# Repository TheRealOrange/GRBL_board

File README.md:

# GRBL_board

## Introduction

This is a PCB designed to run [GRBL](https://github.com/gnea/grbl), an open source CNC control software that is designed and optimised for Arduino. This board uses [GRBL-Mega](https://github.com/gnea/grbl-Mega), which is a version of GRBL that can run on the ATMEGA-2560, used in the Arduino Mega. This implementation allows GRBL to have a larger buffer size, since the ATMEGA-328P that GRBL was originally designed for has severe memory limitations.

This board design incorporates several additional features, such as:

- Designed for SPI configured Trinamic stepper drivers such as the TMC5160, TMC2130, etc.
- Ability to change the mirrored axis (X, Y or Z) via software (supports software configurable gantry levelling)
- All inputs and limit switch inputs wired with optocouplers, designed for normally open switches
- Onboard 12V 2A regulator, accepting 20-32VDC input
- Speed control for industrial VFDs, with a standard 4-20mA current loop for spindle speed control
- Sink logic for spindle control
- Possible sensorless homing using Trinamic drivers (not ideal since it only emulates a limit switch)

The goal is to accomplish this with minimal editing of the GRBL code, thus to do so an additional ATMEGA-328P is added on the board to enable the additional features.

## Connections

This board is designed with the aim of being as compatible as possible with the default GRBL, and as such, the pins are wired to follow the default GRBL-Mega pinout, as shown.

## Trinamic Drivers

Trinamic stepper motor drivers are exceptional in terms of performance and efficiency, incorporating advanced features that enable steppers to run cooler and with near silent operation. 

However, the tricky bit is that they are not a plug an play solution unlike other stepper drivers like the DRV8825 or the A4988 drivers. The drivers haveto be configured whenever they are powered up. To accomplish this, the separate ATMEGA-328P is used to communicate with the drivers via SPI in order to configure them.

## Mirrored Axis

Most CNC configurations include one axis which has dual stepper drive. GRBL has limited support for axis mirroring, and usually sacrifices some pins, such as spindle speed control. Thus, via the use of multiplexer ICs and the separate ATMEGA-328P, code can be uploaded to the ATMEGA-328P in order to specify which axis to mirror and whether to do gantry levelling for that axis.

To accomplish gantry levelling, the ATMEGA-328P will check the two limit switches on the mirrored axis, and if only one switch is triggered, the corresponding stepper's STEP pin will be held low, preventing it from moving until both switches are triggered. Once both limit switches are triggered, the limit switch signal will be sent to the GRBL controller running on the ATMEGA-2560.

## Inputs

Previously, I had an extremely bad experience with EMI on the limit switch lines when building a CNC, thus I decided to include an optocoupler on each input of the CNC controller. Although the switches are still normally open, the optocoupler requires current to drive the LED and thus it is nearly impossible for EMI to trigger the optocoupler. This should make the CNC much more robust against EMI, and it is possible to change the switches to normally closed by modifying GRBL.

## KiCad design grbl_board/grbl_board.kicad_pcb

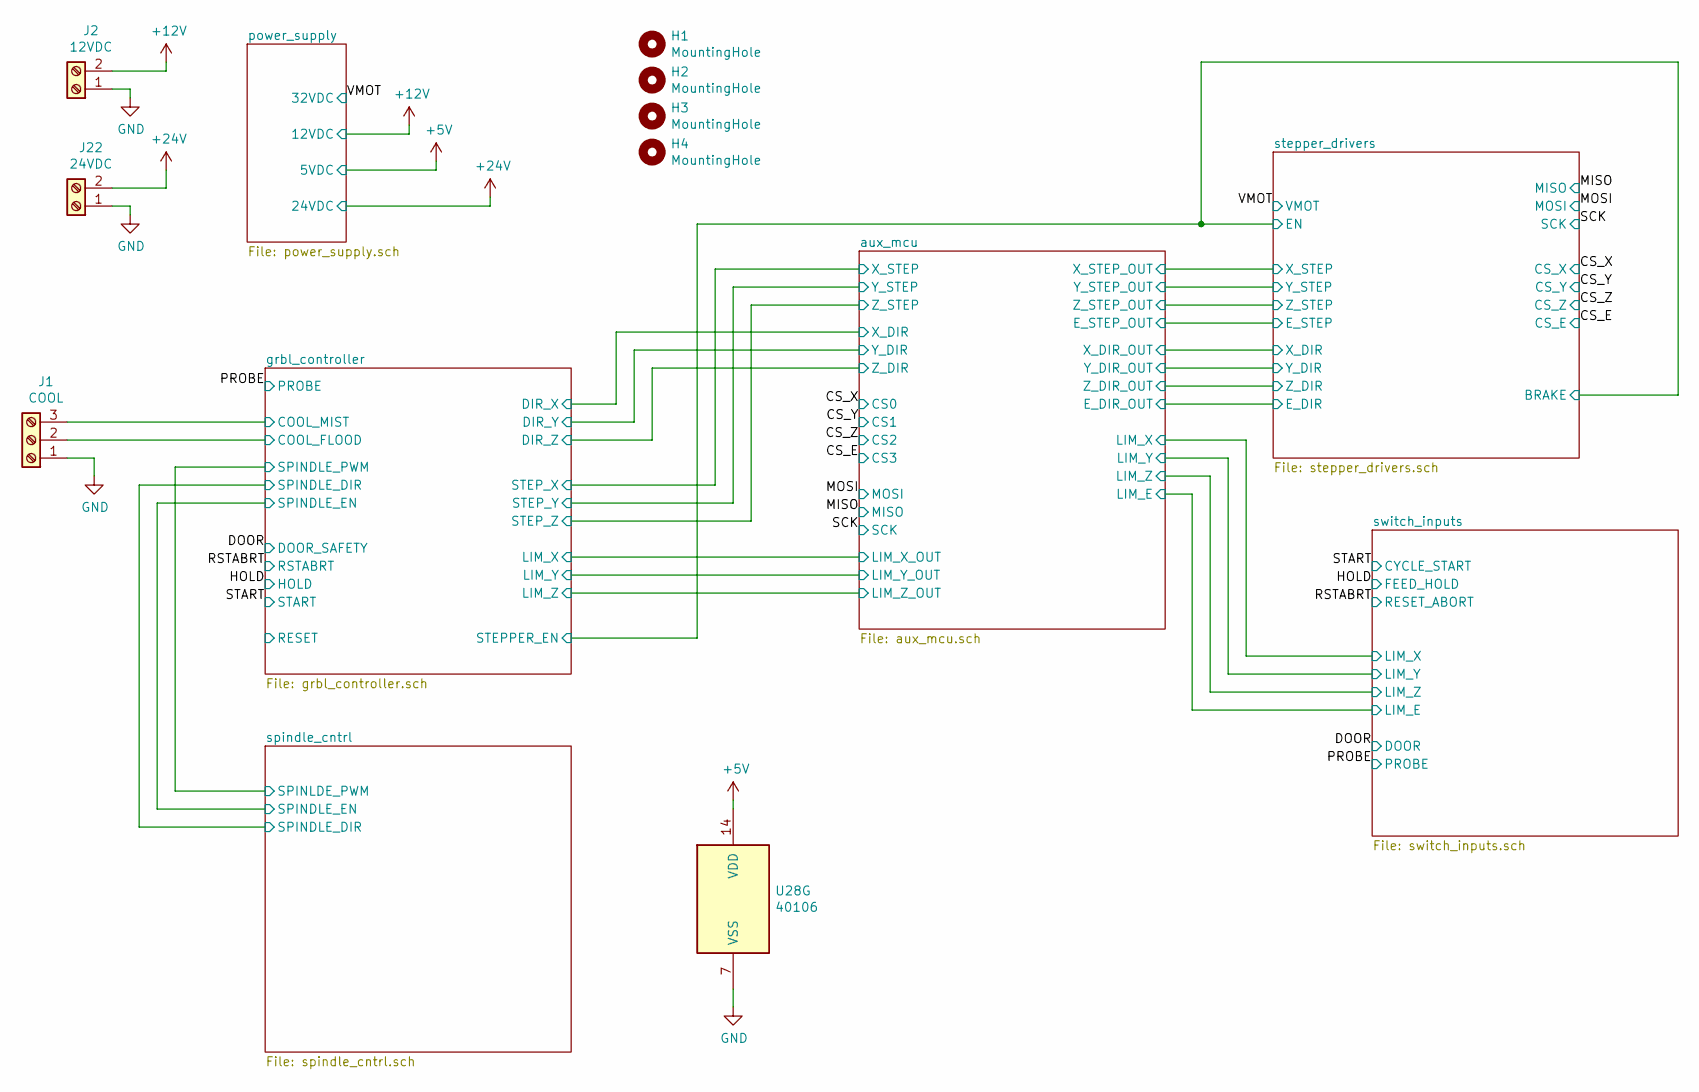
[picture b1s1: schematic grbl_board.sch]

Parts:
H1, H2, H3, H4: MountingHole; MountingHole_3.2mm_M3_Pad
J1: COOL; PhoenixContact_MC_1,5_3-G-3.81_1x03_P3.81mm_Horizontal; Digikey Part No. ED2809-ND
J2: 12VDC; PhoenixContact_MC_1,5_2-G-3.81_1x02_P3.81mm_Horizontal; Digikey Part No. ED2808-ND
J22: 24VDC; PhoenixContact_MC_1,5_2-G-3.81_1x02_P3.81mm_Horizontal; Digikey Part No. ED2808-ND
U28: 40106; TSSOP-14_4.4x5mm_P0.65mm; Digikey Part No. HEF40106BTT,112-ND

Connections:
+5V: U28.14 (VDD); also elsewhere on the board
+12V: J2.2; also elsewhere on the board
+24V: J22.2; also elsewhere on the board
/grbl_controller/COOL_FLOOD: J1.2; also elsewhere on the board
/grbl_controller/COOL_MIST: J1.3; also elsewhere on the board
GND: J1.1, J2.1, J22.1, U28.7 (VSS); also elsewhere on the board

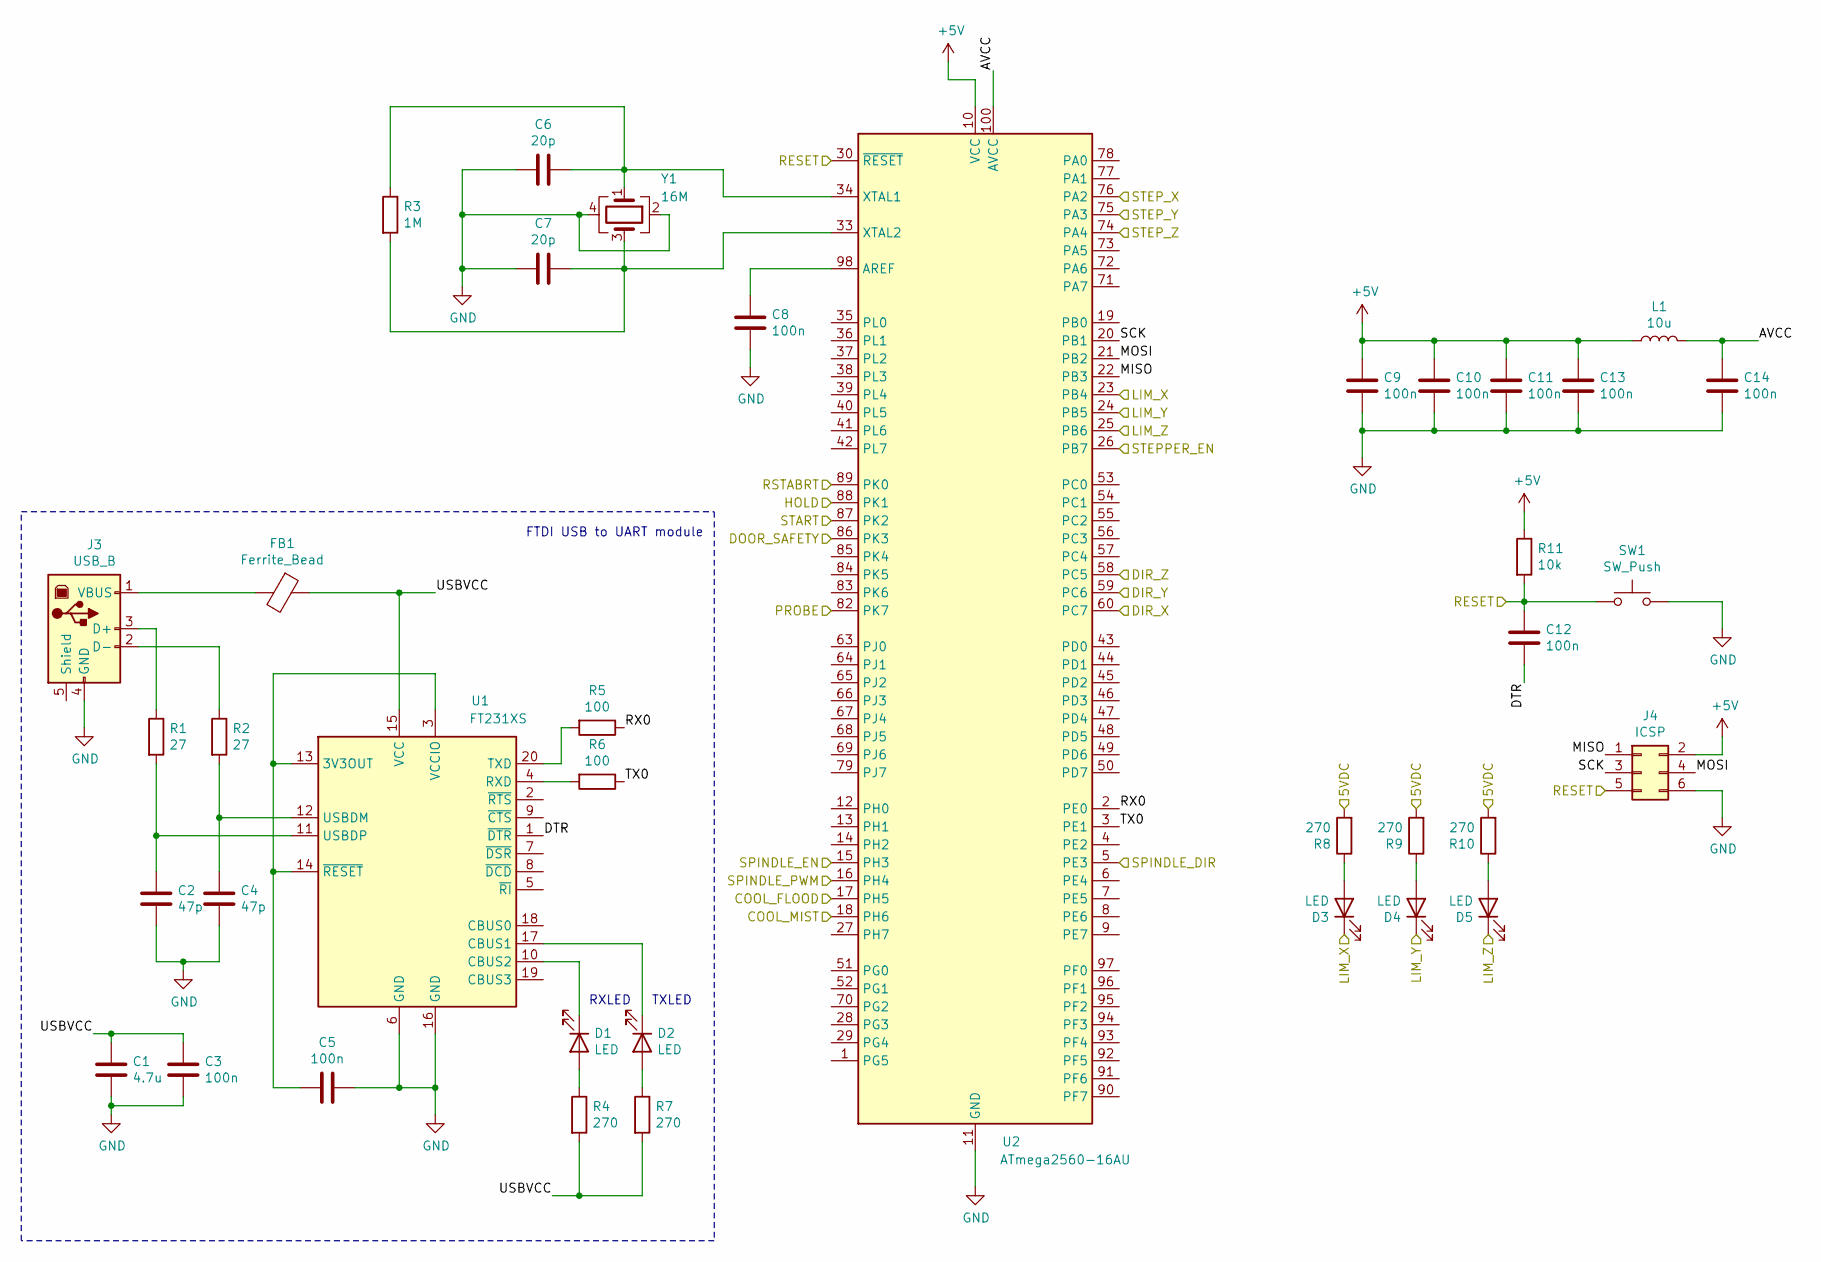
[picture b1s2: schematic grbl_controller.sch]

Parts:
C1: 4.7u; C_1206_3216Metric_Pad1.33x1.80mm_HandSolder; Digikey Part No. 1276-6781-1-ND
C2, C4: 47p; C_0402_1005Metric_Pad0.74x0.62mm_HandSolder; Digikey Part No. 1276-1699-1-ND
C3, C5, C8, C9, C10, C11, C12, C13, C14: 100n; C_0603_1608Metric_Pad1.05x0.95mm_HandSolder; Digikey Part No. 1276-1941-1-ND
C6, C7: 20p; C_0603_1608Metric_Pad1.05x0.95mm_HandSolder; Digikey Part No. 1276-1187-1-ND
D1, D2: LED; LED_1206_3216Metric_Pad1.42x1.75mm_HandSolder; Digikey Part No. 404-1042-1-ND
D3, D4, D5: LED; LED_1206_3216Metric_Pad1.42x1.75mm_HandSolder; Digikey Part No. 404-1046-1-ND
FB1: Ferrite_Bead; C_0603_1608Metric_Pad1.05x0.95mm_HandSolder; Digikey Part No. 732-1591-1-ND
J3: USB_B; USB_B_OST_USB-B1HSxx_Horizontal; Digikey Part No. 380-1492-ND
J4: ICSP; PinHeader_2x03_P2.54mm_Vertical; Digikey Part No. 609-3234-ND
L1: 10u; L_0805_2012Metric_Pad1.05x1.20mm_HandSolder; Digikey Part No. 490-4029-1-ND
R1, R2: 27; R_0603_1608Metric_Pad0.98x0.95mm_HandSolder; Digikey Part No. 311-27GRCT-ND
R3: 1M; R_0603_1608Metric_Pad0.98x0.95mm_HandSolder; Digikey Part No. 311-1.0MGRCT-ND
R4, R7, R8, R9, R10: 270; R_0805_2012Metric_Pad1.15x1.40mm_HandSolder; Digikey Part No. YAG6172CT-ND
R5, R6: 100; R_0603_1608Metric_Pad0.98x0.95mm_HandSolder; Digikey Part No. 311-100GRCT-ND
R11: 10k; R_0805_2012Metric_Pad1.15x1.40mm_HandSolder; Digikey Part No. 311-10KARCT-ND
SW1: SW_Push; SW_Push_1P1T_NO_6x6mm_H9.5mm; Digikey Part No. EG2526CT-ND
U1: FT231XS; SSOP-20_3.9x8.7mm_P0.635mm; Digikey Part No. 768-1129-1-ND
U2: ATmega2560-16AU; TQFP-100_14x14mm_P0.5mm; Digikey Part No. ATMEGA2560-16AU-ND
Y1: 16M; Crystal_SMD_SeikoEpson_TSX3225-4Pin_3.2x2.5mm_HandSoldering; Digikey Part No. SER4372CT-ND

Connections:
+5V: C9.1, C10.1, C11.1, C13.1, J4.2, L1.1, R11.1, U2.10 (VCC), U2.31 (VCC), U2.61 (VCC), U2.80 (VCC); also elsewhere on the board
/DOOR: U2.86 (PK3); also elsewhere on the board
/HOLD: U2.88 (PK1); also elsewhere on the board
/PROBE: U2.82 (PK7); also elsewhere on the board
/RSTABRT: U2.89 (PK0); also elsewhere on the board
/START: U2.87 (PK2); also elsewhere on the board
/grbl_controller/5VDC: R8.2, R9.2, R10.2
/grbl_controller/AVCC: C14.1, L1.2, U2.100 (AVCC)
/grbl_controller/COOL_FLOOD: U2.17 (PH5); also elsewhere on the board
/grbl_controller/COOL_MIST: U2.18 (PH6); also elsewhere on the board
/grbl_controller/DIR_X: U2.60 (PC7); also elsewhere on the board
/grbl_controller/DIR_Y: U2.59 (PC6); also elsewhere on the board
/grbl_controller/DIR_Z: U2.58 (PC5); also elsewhere on the board
/grbl_controller/DTR: C12.2, U1.1 (~DTR)
/grbl_controller/LIM_X: D3.1 (K), U2.23 (PB4); also elsewhere on the board
/grbl_controller/LIM_Y: D4.1 (K), U2.24 (PB5); also elsewhere on the board
/grbl_controller/LIM_Z: D5.1 (K), U2.25 (PB6); also elsewhere on the board
/grbl_controller/MISO: J4.1, U2.22 (PB3)
/grbl_controller/MOSI: J4.4, U2.21 (PB2)
/grbl_controller/RESET: C12.1, J4.5, R11.2, SW1.1, U2.30 (~RESET)
/grbl_controller/RX0: R5.1, U2.2 (PE0)
/grbl_controller/SCK: J4.3, U2.20 (PB1)
/grbl_controller/SPINDLE_DIR: U2.5 (PE3); also elsewhere on the board
/grbl_controller/SPINDLE_EN: U2.15 (PH3); also elsewhere on the board
/grbl_controller/SPINDLE_PWM: U2.16 (PH4); also elsewhere on the board
/grbl_controller/STEP_X: U2.76 (PA2); also elsewhere on the board
/grbl_controller/STEP_Y: U2.75 (PA3); also elsewhere on the board
/grbl_controller/STEP_Z: U2.74 (PA4); also elsewhere on the board
/grbl_controller/TX0: R6.1, U2.3 (PE1)
/grbl_controller/USBVCC: C1.1, C3.1, FB1.1, R4.2, R7.2, U1.15 (VCC)
/stepper_drivers/BRAKE: U2.26 (PB7); also elsewhere on the board
GND: C1.2, C2.2, C3.2, C4.2, C5.1, C6.2, C7.2, C8.1, C9.2, C10.2, C11.2, C13.2, C14.2, J3.4 (GND), J4.6, SW1.2, U1.6 (GND), U1.16 (GND), U2.11 (GND), U2.32 (GND), U2.62 (GND), U2.81 (GND), U2.99 (GND), Y1.2, Y1.4; also elsewhere on the board
unnamed: C2.1, R1.2, U1.11 (USBDP)
unnamed: C4.1, R2.2, U1.12 (USBDM)
unnamed: C5.2, U1.3 (VCCIO), U1.13 (3V3OUT), U1.14 (~RESET)
unnamed: C6.1, R3.1, U2.34 (XTAL1), Y1.1
unnamed: C7.1, R3.2, U2.33 (XTAL2), Y1.3
unnamed: C8.2, U2.98 (AREF)
unnamed: D1.1 (K), U1.10 (CBUS2)
unnamed: D1.2 (A), R4.1
unnamed: D2.1 (K), U1.17 (CBUS1)
unnamed: D2.2 (A), R7.1
unnamed: D3.2 (A), R8.1
unnamed: D4.2 (A), R9.1
unnamed: D5.2 (A), R10.1
unnamed: FB1.2, J3.1 (VBUS)
unnamed: J3.2 (D-), R2.1
unnamed: J3.3 (D+), R1.1
unnamed: R5.2, U1.20 (TXD)
unnamed: R6.2, U1.4 (RXD)

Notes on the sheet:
TXLED
RXLED
FTDI USB to UART module

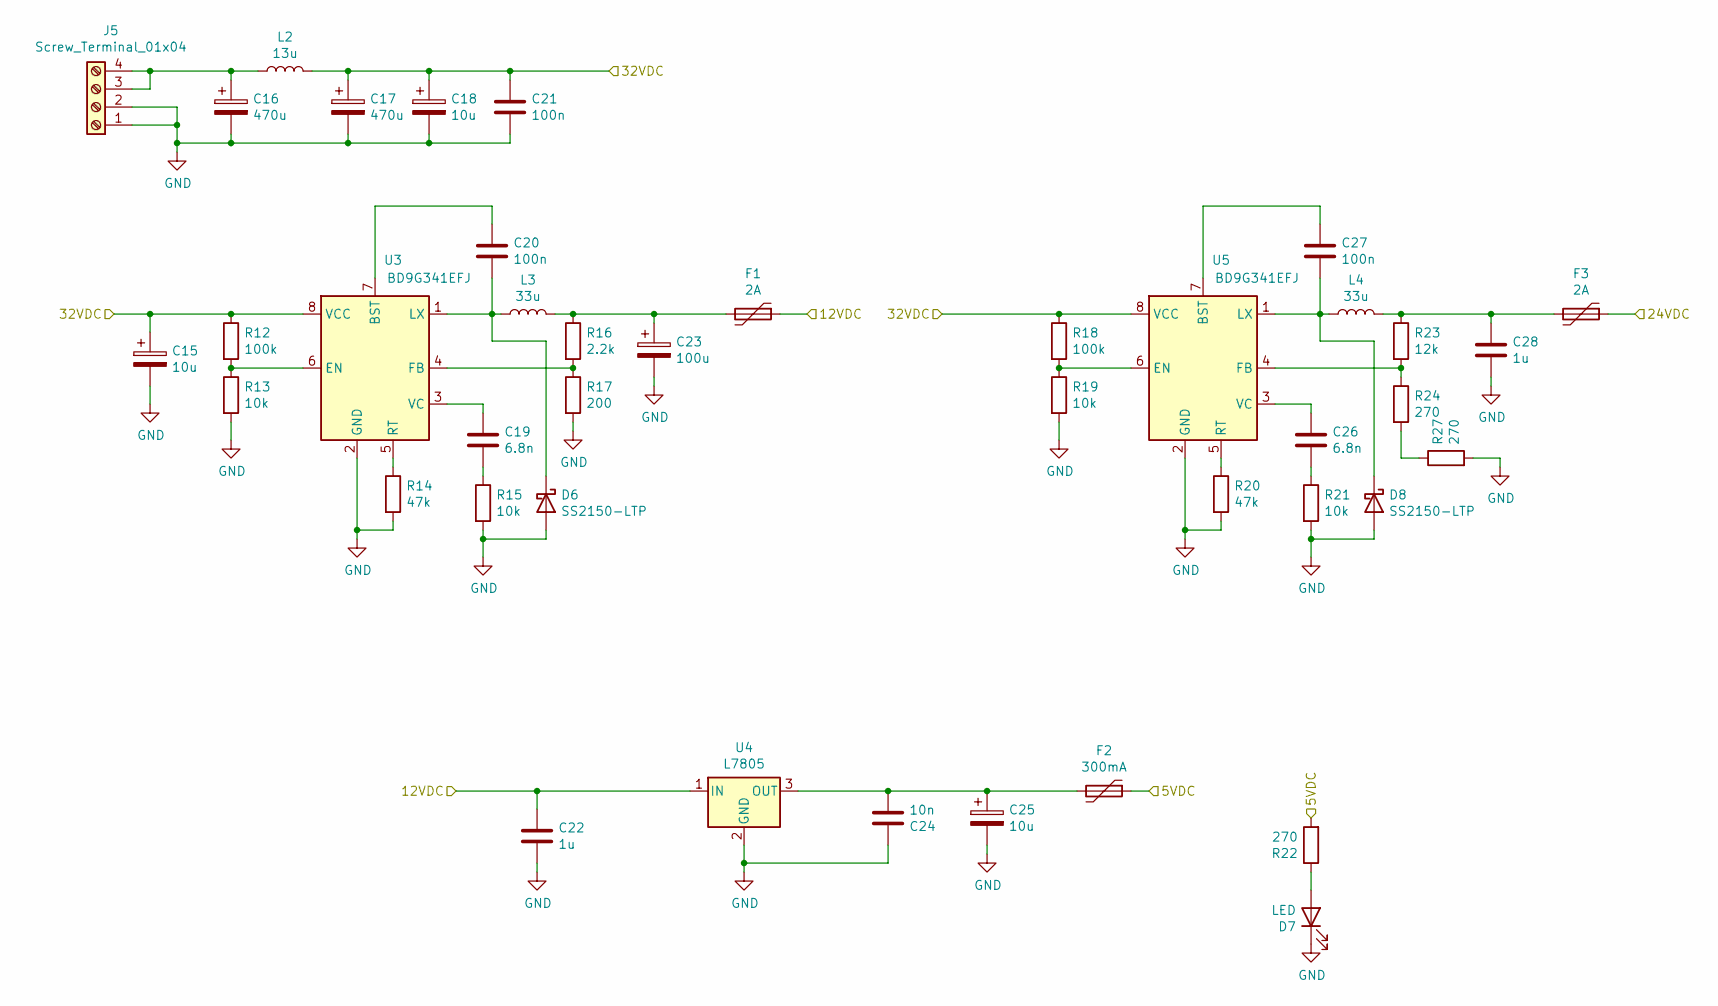
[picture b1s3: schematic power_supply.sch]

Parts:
C15, C18, C25: 10u; CP_Radial_D8.0mm_P3.50mm; Digikey Part No. 495-75596-ND
C16, C17: 470u; CP_Radial_D12.5mm_P5.00mm; Digikey Part No. 495-76603-ND
C19, C26: 6.8n; C_0402_1005Metric_Pad0.74x0.62mm_HandSolder; Digikey Part No. 1276-CL05B682KB5VPNCCT-ND
C20, C21, C27: 100n; C_0603_1608Metric_Pad1.05x0.95mm_HandSolder; Digikey Part No. 1276-1941-1-ND
C22, C28: 1u; C_1206_3216Metric_Pad1.33x1.80mm_HandSolder; Digikey Part No. 1276-1204-1-ND
C23: 100u; CP_Radial_D8.0mm_P3.50mm; Digikey Part No. 399-6119-ND
C24: 10n; C_0603_1608Metric_Pad1.08x0.95mm_HandSolder; Digikey Part No. 1276-1009-1-ND
D6, D8: SS2150-LTP; D_SMA_Handsoldering; Digikey Part No. SS2150-LTPMSCT-ND
D7: LED; LED_1206_3216Metric_Pad1.42x1.75mm_HandSolder; Digikey Part No. 404-1046-1-ND
F1, F3: 2A; Fuse_Bourns_MF-RHT200; Digikey Part No. 118-MF-RHT200/32-0-ND
F2: 300mA; Fuse_1812_4532Metric_Castellated; Digikey Part No. 507-1758-1-ND
J5: Screw_Terminal_01x04; PhoenixContact_MC_1,5_4-G-3.81_1x04_P3.81mm_Horizontal; Digikey Part No. ED2810-ND
L2: 13u; L_Wuerth_HCI-1365; Digikey Part No. 732-1140-1-ND
L3, L4: 33u; L_Vishay_IHLP-4040; Digikey Part No. 541-2273-1-ND
R12, R18: 100k; R_0603_1608Metric_Pad0.98x0.95mm_HandSolder; Digikey Part No. 311-100KGRCT-ND
R13, R15, R19, R21: 10k; R_0805_2012Metric_Pad1.15x1.40mm_HandSolder; Digikey Part No. 311-10KARCT-ND
R14, R20: 47k; R_0805_2012Metric_Pad1.15x1.40mm_HandSolder; Digikey Part No. 311-47KARCT-ND
R16: 2.2k; R_0603_1608Metric_Pad0.98x0.95mm_HandSolder; Digikey Part No. 311-2.2KGRCT-ND
R17: 200; R_0603_1608Metric_Pad0.98x0.95mm_HandSolder; Digikey Part No. 311-200GRCT-ND
R22, R24, R27: 270; R_0805_2012Metric_Pad1.15x1.40mm_HandSolder; Digikey Part No. YAG6172CT-ND
R23: 12k; R_0805_2012Metric_Pad1.15x1.40mm_HandSolder; Digikey Part No. 311-12KARCT-ND
U3, U5: BD9G341EFJ; HTSOP-8-1EP_3.9x4.9mm_P1.27mm_EP2.4x3.2mm_ThermalVias; Digikey Part No. BD9G341AEFJ-E2CT-ND
U4: L7805; TO-263-2; Digikey Part No. 497-1170-1-ND

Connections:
+5V: F2.1, R22.2; also elsewhere on the board
+12V: C22.1, F1.1, U4.1 (IN); also elsewhere on the board
+24V: F3.1; also elsewhere on the board
/VMOT: C15.1, C17.1, C18.1, C21.1, L2.2, R12.1, R18.1, U3.8 (VCC), U5.8 (VCC); also elsewhere on the board
GND: C15.2, C16.2, C17.2, C18.2, C21.2, C22.2, C23.2, C24.1, C25.2, C28.2, D6.2 (A), D7.1 (K), D8.2 (A), J5.1, J5.2, R13.2, R14.2, R15.2, R17.2, R19.2, R20.2, R21.2, R27.2, U3.2 (GND), U4.2 (GND), U5.2 (GND); also elsewhere on the board
unnamed: C16.1, J5.3, J5.4, L2.1
unnamed: C19.1, U3.3 (VC)
unnamed: C19.2, R15.1
unnamed: C20.1, U3.7 (BST)
unnamed: C20.2, D6.1 (K), L3.1, U3.1 (LX)
unnamed: C23.1, F1.2, L3.2, R16.1
unnamed: C24.2, C25.1, F2.2, U4.3 (OUT)
unnamed: C26.1, U5.3 (VC)
unnamed: C26.2, R21.1
unnamed: C27.1, U5.7 (BST)
unnamed: C27.2, D8.1 (K), L4.1, U5.1 (LX)
unnamed: C28.1, F3.2, L4.2, R23.1
unnamed: D7.2 (A), R22.1
unnamed: R12.2, R13.1, U3.6 (EN)
unnamed: R14.1, U3.5 (RT)
unnamed: R16.2, R17.1, U3.4 (FB)
unnamed: R18.2, R19.1, U5.6 (EN)
unnamed: R20.1, U5.5 (RT)
unnamed: R23.2, R24.1, U5.4 (FB)
unnamed: R24.2, R27.1

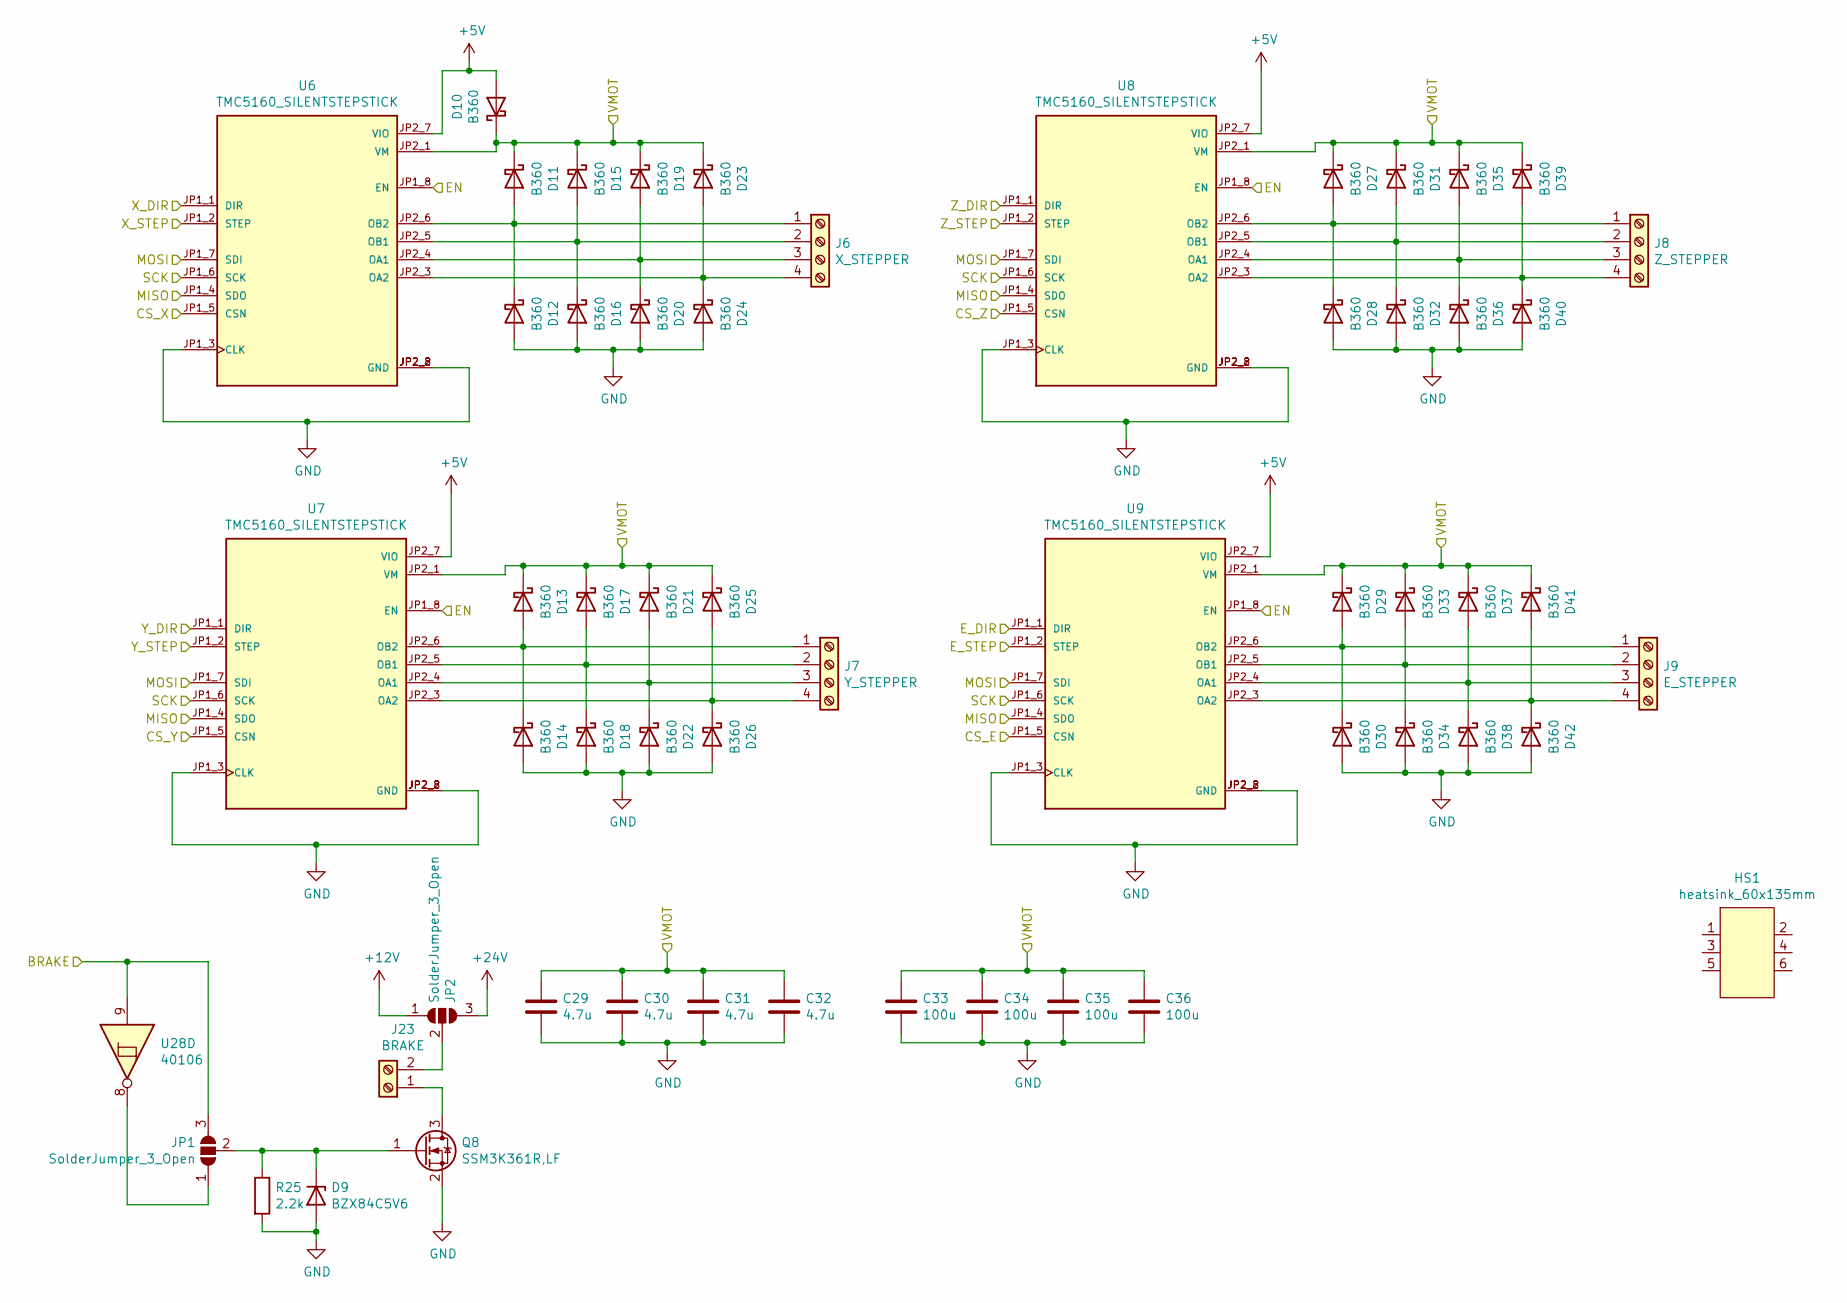
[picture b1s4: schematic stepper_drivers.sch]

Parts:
C29, C30, C31, C32: 4.7u; C_1206_3216Metric_Pad1.33x1.80mm_HandSolder; Digikey Part No. 1276-6781-1-ND
C33, C34, C35, C36: 100u; CP_Elec_8x10; Digikey Part No. UE107M050HFKTA
D9: BZX84C5V6; D_SOT-23_ANK; Digikey Part No. 1514-BZX84C5V6TRPBFREECT-ND
D10, D11, D12, D13, D14, D15, D16, D17, D18, D19, D20, D21, D22, D23, D24, D25, D26, D27, D28, D29, D30, D31, D32, D33, D34, D35, D36, D37, D38, D39, D40, D41, D42: B360; D_SMA_Handsoldering; Digikey Part No. CD214A-B360RCT-ND
HS1: heatsink_60x135mm
J6: X_STEPPER; PhoenixContact_MC_1,5_4-G-3.81_1x04_P3.81mm_Horizontal; Digikey Part No. ED2810-ND
J7: Y_STEPPER; PhoenixContact_MC_1,5_4-G-3.81_1x04_P3.81mm_Horizontal; Digikey Part No. ED2810-ND
J8: Z_STEPPER; PhoenixContact_MC_1,5_4-G-3.81_1x04_P3.81mm_Horizontal; Digikey Part No. ED2810-ND
J9: E_STEPPER; PhoenixContact_MC_1,5_4-G-3.81_1x04_P3.81mm_Horizontal; Digikey Part No. ED2810-ND
J23: BRAKE; PhoenixContact_MC_1,5_2-G-3.81_1x02_P3.81mm_Horizontal; Digikey Part No. ED2808-ND
JP1, JP2: SolderJumper_3_Open; SolderJumper-3_P1.3mm_Open_RoundedPad1.0x1.5mm
Q8: SSM3K361R,LF; SOT-23; Digikey Part No. SSM3K361RLFCT-ND
R25: 2.2k; R_0603_1608Metric_Pad0.98x0.95mm_HandSolder; Digikey Part No. 311-2.2KGRCT-ND
U6, U7, U8, U9: TMC5160_SILENTSTEPSTICK; PARTREV v11; Digikey Part No. 1460-TMC5160SILENTSTEPSTICK-ND
U28: 40106

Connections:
+5V: D10.2 (A), U6.JP2_7 (VIO), U7.JP2_7 (VIO), U8.JP2_7 (VIO), U9.JP2_7 (VIO); also elsewhere on the board
+12V: JP2.1 (A); also elsewhere on the board
+24V: JP2.3 (B); also elsewhere on the board
/CS_E: U9.JP1_5 (CSN); also elsewhere on the board
/CS_X: U6.JP1_5 (CSN); also elsewhere on the board
/CS_Y: U7.JP1_5 (CSN); also elsewhere on the board
/CS_Z: U8.JP1_5 (CSN); also elsewhere on the board
/MISO: U6.JP1_4 (SDO), U7.JP1_4 (SDO), U8.JP1_4 (SDO), U9.JP1_4 (SDO); also elsewhere on the board
/MOSI: U6.JP1_7 (SDI), U7.JP1_7 (SDI), U8.JP1_7 (SDI), U9.JP1_7 (SDI); also elsewhere on the board
/SCK: U6.JP1_6 (SCK), U7.JP1_6 (SCK), U8.JP1_6 (SCK), U9.JP1_6 (SCK); also elsewhere on the board
/VMOT: C29.1, C30.1, C31.1, C32.1, C33.1, C34.1, C35.1, C36.1, D10.1 (K), D11.1 (K), D13.1 (K), D15.1 (K), D17.1 (K), D19.1 (K), D21.1 (K), D23.1 (K), D25.1 (K), D27.1 (K), D29.1 (K), D31.1 (K), D33.1 (K), D35.1 (K), D37.1 (K), D39.1 (K), D41.1 (K), U6.JP2_1 (VM), U7.JP2_1 (VM), U8.JP2_1 (VM), U9.JP2_1 (VM); also elsewhere on the board
/grbl_controller/DIR_X: U6.JP1_1 (DIR); also elsewhere on the board
/grbl_controller/DIR_Y: U7.JP1_1 (DIR); also elsewhere on the board
/grbl_controller/DIR_Z: U8.JP1_1 (DIR); also elsewhere on the board
/stepper_drivers/BRAKE: JP1.3 (B), U6.JP1_8 (EN), U7.JP1_8 (EN), U8.JP1_8 (EN), U9.JP1_8 (EN), U28.9; also elsewhere on the board
/stepper_drivers/E_DIR: U9.JP1_1 (DIR); also elsewhere on the board
/stepper_drivers/E_STEP: U9.JP1_2 (STEP); also elsewhere on the board
/stepper_drivers/X_STEP: U6.JP1_2 (STEP); also elsewhere on the board
/stepper_drivers/Y_STEP: U7.JP1_2 (STEP); also elsewhere on the board
/stepper_drivers/Z_STEP: U8.JP1_2 (STEP); also elsewhere on the board
GND: C29.2, C30.2, C31.2, C32.2, C33.2, C34.2, C35.2, C36.2, D9.2 (A), D12.2 (A), D14.2 (A), D16.2 (A), D18.2 (A), D20.2 (A), D22.2 (A), D24.2 (A), D26.2 (A), D28.2 (A), D30.2 (A), D32.2 (A), D34.2 (A), D36.2 (A), D38.2 (A), D40.2 (A), D42.2 (A), Q8.2 (S), R25.2, U6.JP1_3 (CLK), U6.JP2_2 (GND), U6.JP2_8 (GND), U7.JP1_3 (CLK), U7.JP2_2 (GND), U7.JP2_8 (GND), U8.JP1_3 (CLK), U8.JP2_2 (GND), U8.JP2_8 (GND), U9.JP1_3 (CLK), U9.JP2_2 (GND), U9.JP2_8 (GND); also elsewhere on the board
unnamed: D9.1 (K), JP1.2 (C), Q8.1 (G), R25.1
unnamed: D11.2 (A), D12.1 (K), J6.1, U6.JP2_6 (OB2)
unnamed: D13.2 (A), D14.1 (K), J7.1, U7.JP2_6 (OB2)
unnamed: D15.2 (A), D16.1 (K), J6.2, U6.JP2_5 (OB1)
unnamed: D17.2 (A), D18.1 (K), J7.2, U7.JP2_5 (OB1)
unnamed: D19.2 (A), D20.1 (K), J6.3, U6.JP2_4 (OA1)
unnamed: D21.2 (A), D22.1 (K), J7.3, U7.JP2_4 (OA1)
unnamed: D23.2 (A), D24.1 (K), J6.4, U6.JP2_3 (OA2)
unnamed: D25.2 (A), D26.1 (K), J7.4, U7.JP2_3 (OA2)
unnamed: D27.2 (A), D28.1 (K), J8.1, U8.JP2_6 (OB2)
unnamed: D29.2 (A), D30.1 (K), J9.1, U9.JP2_6 (OB2)
unnamed: D31.2 (A), D32.1 (K), J8.2, U8.JP2_5 (OB1)
unnamed: D33.2 (A), D34.1 (K), J9.2, U9.JP2_5 (OB1)
unnamed: D35.2 (A), D36.1 (K), J8.3, U8.JP2_4 (OA1)
unnamed: D37.2 (A), D38.1 (K), J9.3, U9.JP2_4 (OA1)
unnamed: D39.2 (A), D40.1 (K), J8.4, U8.JP2_3 (OA2)
unnamed: D41.2 (A), D42.1 (K), J9.4, U9.JP2_3 (OA2)
unnamed: J23.1, Q8.3 (D)
unnamed: J23.2, JP2.2 (C)
unnamed: JP1.1 (A), U28.8

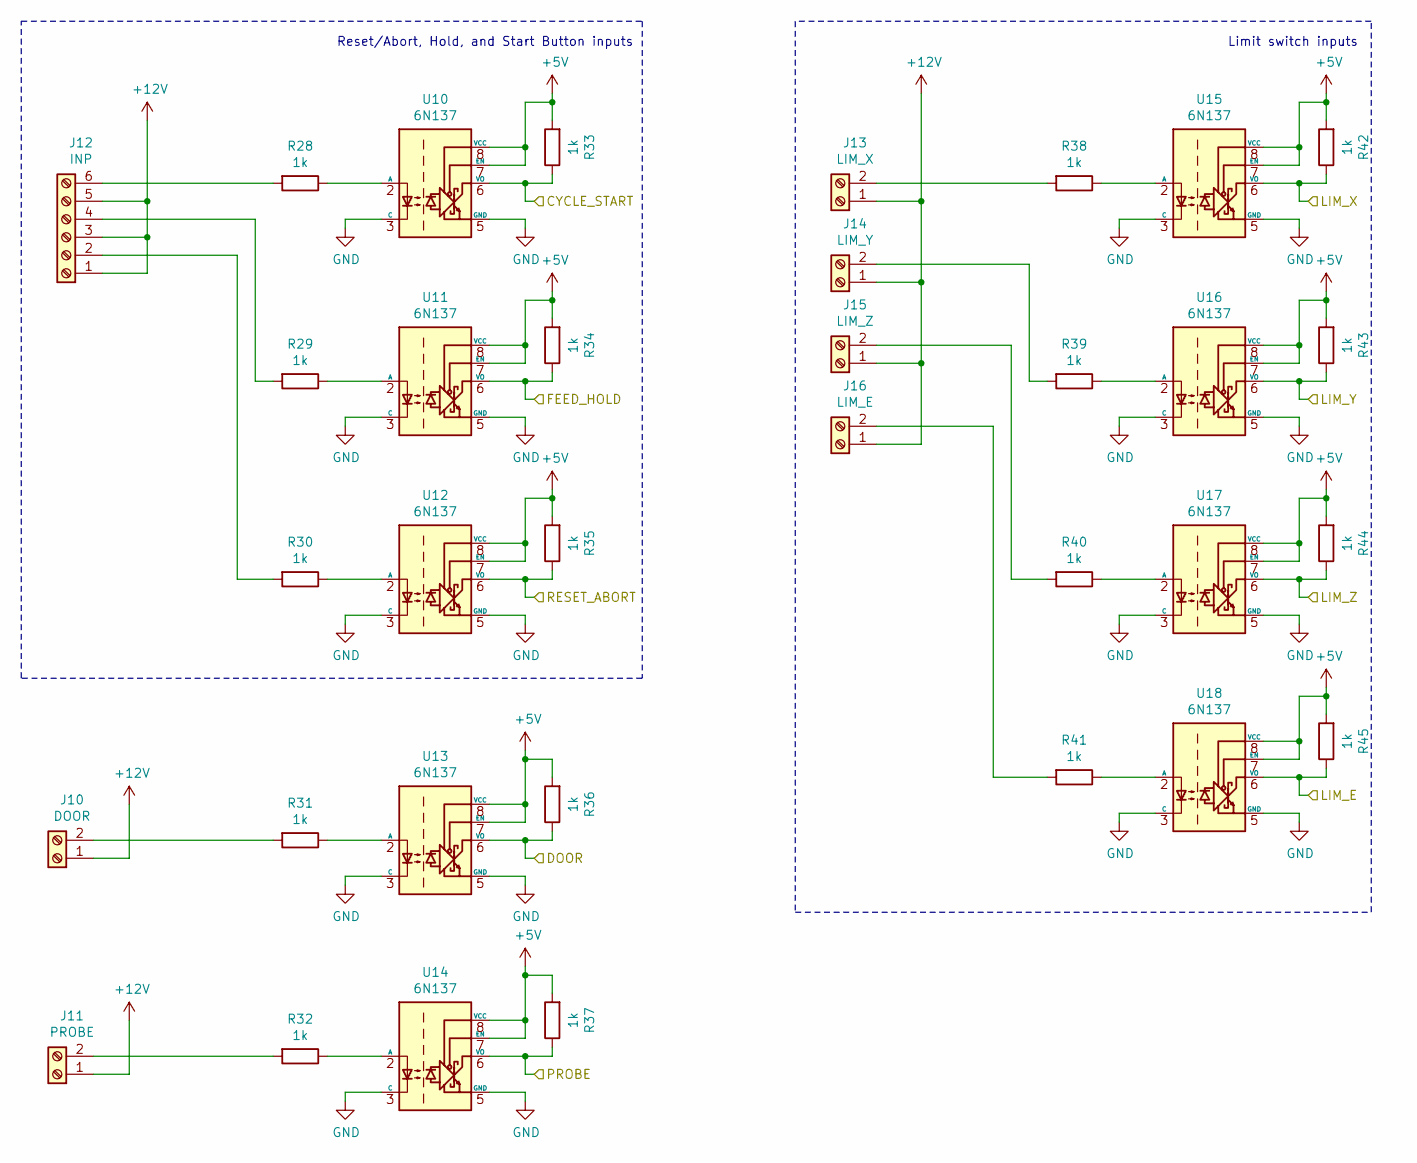
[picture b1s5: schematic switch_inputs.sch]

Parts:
J10: DOOR; PhoenixContact_MC_1,5_2-G-3.81_1x02_P3.81mm_Horizontal; Digikey Part No. ED2808-ND
J11: PROBE; PhoenixContact_MC_1,5_2-G-3.81_1x02_P3.81mm_Horizontal; Digikey Part No. ED2808-ND
J12: INP; PhoenixContact_MC_1,5_6-G-3.81_1x06_P3.81mm_Horizontal; Digikey Part No. ED2812-ND
J13: LIM_X; PhoenixContact_MC_1,5_2-G-3.81_1x02_P3.81mm_Horizontal; Digikey Part No. ED2808-ND
J14: LIM_Y; PhoenixContact_MC_1,5_2-G-3.81_1x02_P3.81mm_Horizontal; Digikey Part No. ED2808-ND
J15: LIM_Z; PhoenixContact_MC_1,5_2-G-3.81_1x02_P3.81mm_Horizontal; Digikey Part No. ED2808-ND
J16: LIM_E; PhoenixContact_MC_1,5_2-G-3.81_1x02_P3.81mm_Horizontal; Digikey Part No. ED2808-ND
R28, R29, R30, R31, R32, R38, R39, R40, R41: 1k; R_1206_3216Metric_Pad1.30x1.75mm_HandSolder; Digikey Part No. 311-1.0KERCT-ND
R33, R34, R35, R36, R37, R42, R43, R44, R45: 1k; R_0805_2012Metric_Pad1.15x1.40mm_HandSolder; Digikey Part No. 311-10KARCT-ND
U10, U11, U12, U13, U14, U15, U16, U17, U18: 6N137; DIP-8_W7.62mm_Socket; Digikey Part No. 6N137IS-ND

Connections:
+5V: R33.2, R34.2, R35.2, R36.2, R37.2, R42.2, R43.2, R44.2, R45.2, U10.7 (EN), U10.8 (VCC), U11.7 (EN), U11.8 (VCC), U12.7 (EN), U12.8 (VCC), U13.7 (EN), U13.8 (VCC), U14.7 (EN), U14.8 (VCC), U15.7 (EN), U15.8 (VCC), U16.7 (EN), U16.8 (VCC), U17.7 (EN), U17.8 (VCC), U18.7 (EN), U18.8 (VCC); also elsewhere on the board
+12V: J10.1, J11.1, J12.1, J12.3, J12.5, J13.1, J14.1, J15.1, J16.1; also elsewhere on the board
/DOOR: R36.1, U13.6 (VO); also elsewhere on the board
/HOLD: R34.1, U11.6 (VO); also elsewhere on the board
/PROBE: R37.1, U14.6 (VO); also elsewhere on the board
/RSTABRT: R35.1, U12.6 (VO); also elsewhere on the board
/START: R33.1, U10.6 (VO); also elsewhere on the board
/aux_mcu/LIM_E: R45.1, U18.6 (VO); also elsewhere on the board
/aux_mcu/LIM_X: R42.1, U15.6 (VO); also elsewhere on the board
/aux_mcu/LIM_Y: R43.1, U16.6 (VO); also elsewhere on the board
/aux_mcu/LIM_Z: R44.1, U17.6 (VO); also elsewhere on the board
GND: U10.3 (C), U10.5 (GND), U11.3 (C), U11.5 (GND), U12.3 (C), U12.5 (GND), U13.3 (C), U13.5 (GND), U14.3 (C), U14.5 (GND), U15.3 (C), U15.5 (GND), U16.3 (C), U16.5 (GND), U17.3 (C), U17.5 (GND), U18.3 (C), U18.5 (GND); also elsewhere on the board
unnamed: J10.2, R31.2
unnamed: J11.2, R32.2
unnamed: J12.2, R30.2
unnamed: J12.4, R29.2
unnamed: J12.6, R28.2
unnamed: J13.2, R38.2
unnamed: J14.2, R39.2
unnamed: J15.2, R40.2
unnamed: J16.2, R41.2
unnamed: R28.1, U10.2 (A)
unnamed: R29.1, U11.2 (A)
unnamed: R30.1, U12.2 (A)
unnamed: R31.1, U13.2 (A)
unnamed: R32.1, U14.2 (A)
unnamed: R38.1, U15.2 (A)
unnamed: R39.1, U16.2 (A)
unnamed: R40.1, U17.2 (A)
unnamed: R41.1, U18.2 (A)

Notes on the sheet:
Limit switch inputs
Reset/Abort, Hold, and Start Button inputs
